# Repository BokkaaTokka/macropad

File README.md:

# CadPad
**This is my own macropad called CadPad.**

CadPad is designed to provide shortcuts in CAD, but also works for other things by mapping it to anything you want. It is also my very first PCB design.

### Problems I faced
I had a really fun time making the PCB, it was my first time, but thanks to the good introduction an the intuitive software, it turned out pretty well.(I think, we'll see when I get the real ones.)
I'm also completely new to QMK-firmware and compiling. I have done a lot of programming before, mainly with micropython/circuitpython/python, but this was something new. I can't tell how happy I was when the console filled up with [OK].

I wanted to try a kind of mounting that I have never used before. The nut and end of the screw will be covered by a thin plate that also adds some design to the project. This will require me to cut the screws in exact lenghths. The section analysis is slightly outdated, I have for example added some space between the top and base, the vertical ble/pink line.

### BOM
|Unit|Amount|
|:----|:----|
|Cherry MX Switch|9x|
|XIAO rp2040|1x|
|Blank DSA Keycap|9x|
|M3x16 Bolt|4x|
|M3 Nut|4x|
|1N4148 DO-35 Diodes|9x|
|EC11 Rotary Encoder|1x|
|2.54mm straight pin header|18x|
#### I will also use/need
* 3D printed parts
* Custom PCB
* QMK firmware
* Soldering iron

### Current state

I'm done with designing PCB, case and firmware. The current version has two layers, for CAD and normal use, this will be modified later.

Below is a screenshot of the current PCB routing, I had tho change the placing of the diodes, as the may be in the way of the buttons.

### The future
I will definitly change the firmware a bit once I have tested the functionality, add an animation to the OLED and update the keymap. But it will get a lot easier once I have the physical product to test on.

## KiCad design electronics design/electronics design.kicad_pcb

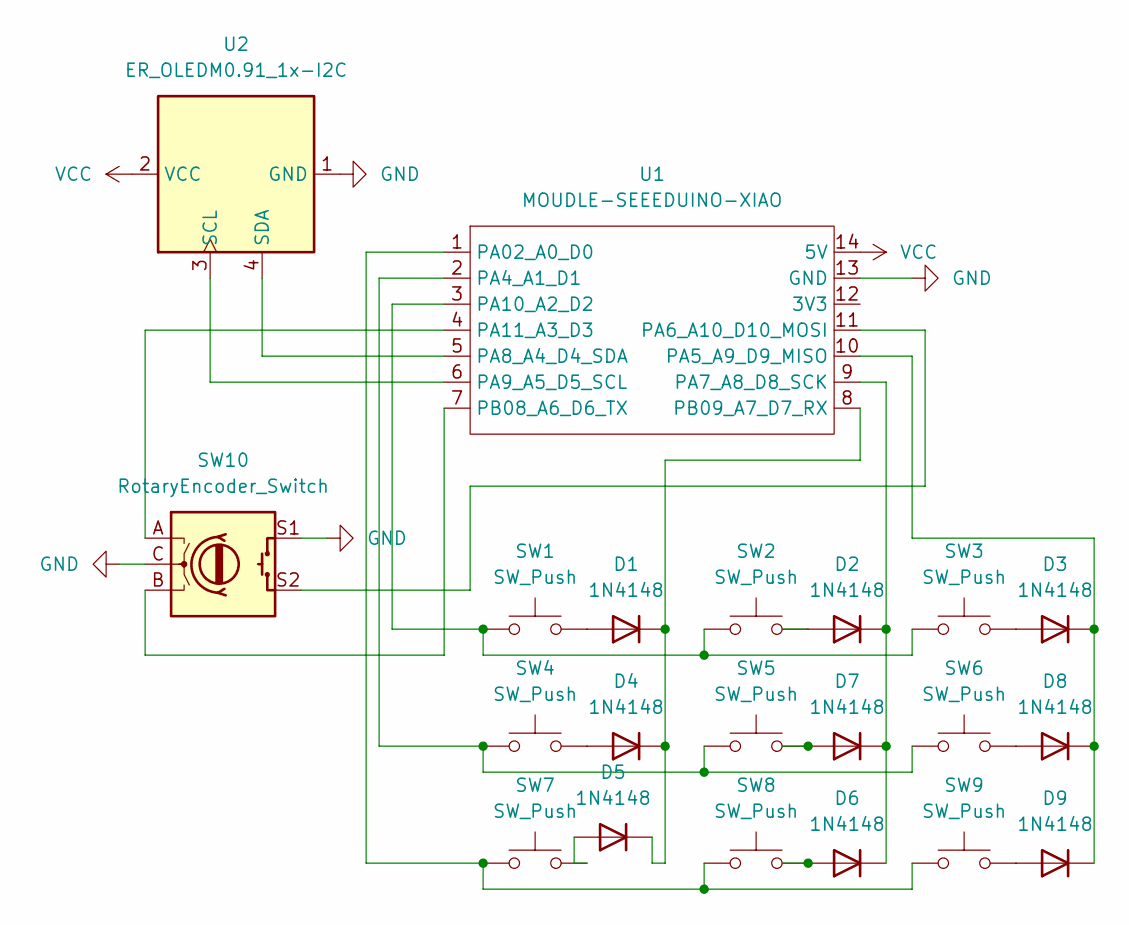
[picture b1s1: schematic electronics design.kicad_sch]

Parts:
D1, D2, D3, D4, D5, D6, D7, D8, D9: 1N4148; D_DO-35_SOD27_P7.62mm_Horizontal
SW1, SW2, SW3, SW4, SW5, SW6, SW7, SW8, SW9: SW_Push; SW_Cherry_MX_1.00u_PCB_centered
SW10: RotaryEncoder_Switch; RotaryEncoder_Alps_EC11E-Switch_Vertical_H20mm
U1: MOUDLE-SEEEDUINO-XIAO; XIAO-Generic-Hybrid-14P-2.54-21X17.8MM
U2: ER_OLEDM0.91_1x-I2C; PinSocket_1x04_P2.54mm_Vertical

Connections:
GND: SW10.C, SW10.S1, U1.13 (GND), U2.1 (GND)
unnamed: D1.2 (A), SW1.2
unnamed: D1.1 (K), D4.1 (K), D5.1 (K), U1.8 (PB09_A7_D7_RX)
unnamed: D2.2 (A), SW2.2
unnamed: D2.1 (K), D6.1 (K), D7.1 (K), U1.9 (PA7_A8_D8_SCK)
unnamed: D3.2 (A), SW3.2
unnamed: D3.1 (K), D8.1 (K), D9.1 (K), U1.10 (PA5_A9_D9_MISO)
unnamed: D4.2 (A), SW4.2
unnamed: D5.2 (A), SW7.2
unnamed: D6.2 (A), SW8.2
unnamed: D7.2 (A), SW5.2
unnamed: D8.2 (A), SW6.2
unnamed: D9.2 (A), SW9.2
unnamed: SW7.1, SW8.1, SW9.1, U1.1 (PA02_A0_D0)
unnamed: SW4.1, SW5.1, SW6.1, U1.2 (PA4_A1_D1)
unnamed: SW10.S2, U1.11 (PA6_A10_D10_MOSI)
unnamed: U1.5 (PA8_A4_D4_SDA), U2.4 (SDA)
unnamed: U1.6 (PA9_A5_D5_SCL), U2.3 (SCL)
unnamed: SW1.1, SW2.1, SW3.1, U1.3 (PA10_A2_D2)
unnamed: SW10.A, U1.4 (PA11_A3_D3)
unnamed: SW10.B, U1.7 (PB08_A6_D6_TX)
VCC: U1.14 (5V), U2.2 (VCC)

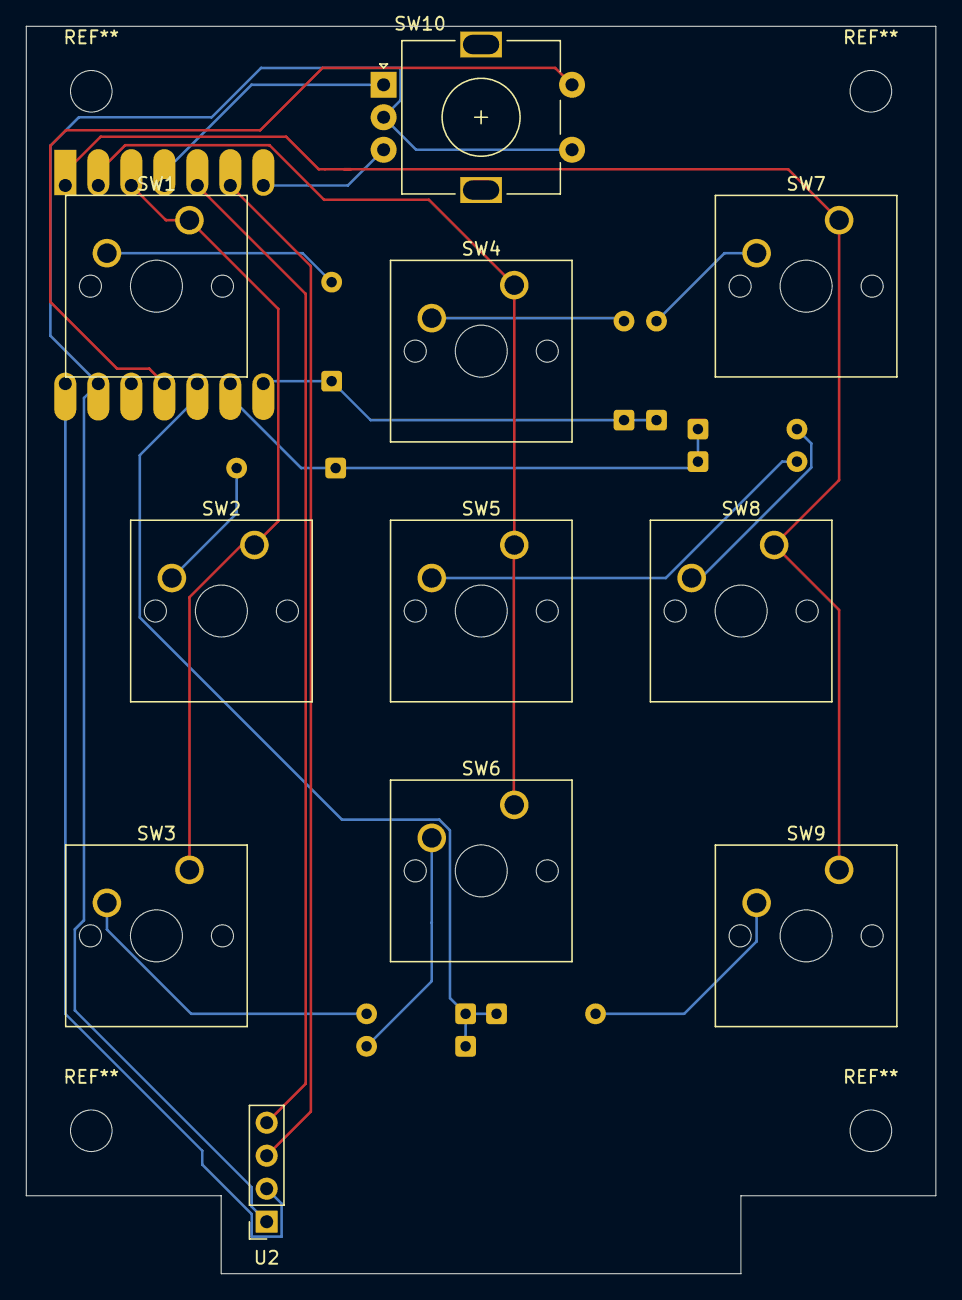
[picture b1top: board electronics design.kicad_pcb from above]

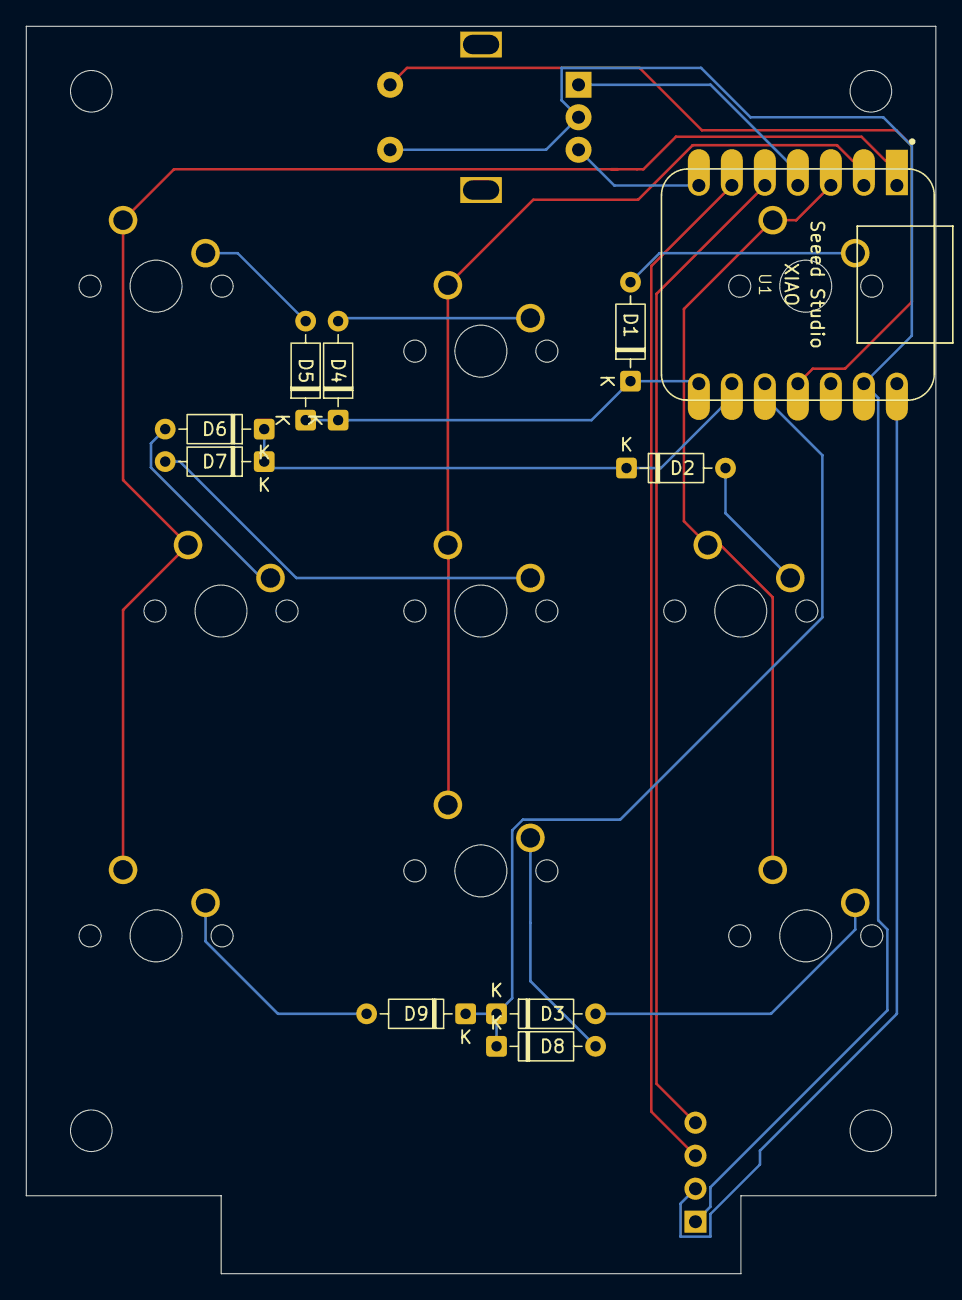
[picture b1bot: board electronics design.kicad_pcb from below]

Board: 2 copper layers, 70.0 x 96.0 mm, 21 parts (10 on the bottom side), 22 nets.

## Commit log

2026-03-29 Created the repo.
2026-03-30 Added production and firmware
2026-03-30 added README
2026-03-30 Replaced .paint file.
2026-03-30 Update README.md
    Fixed what I had missed in the readme.
2026-04-01 Changed the position of the diodes to make space for the buttons.
2026-04-01 Change image caption for PCB routing screenshot
    Updated image reference in README for PCB routing.
